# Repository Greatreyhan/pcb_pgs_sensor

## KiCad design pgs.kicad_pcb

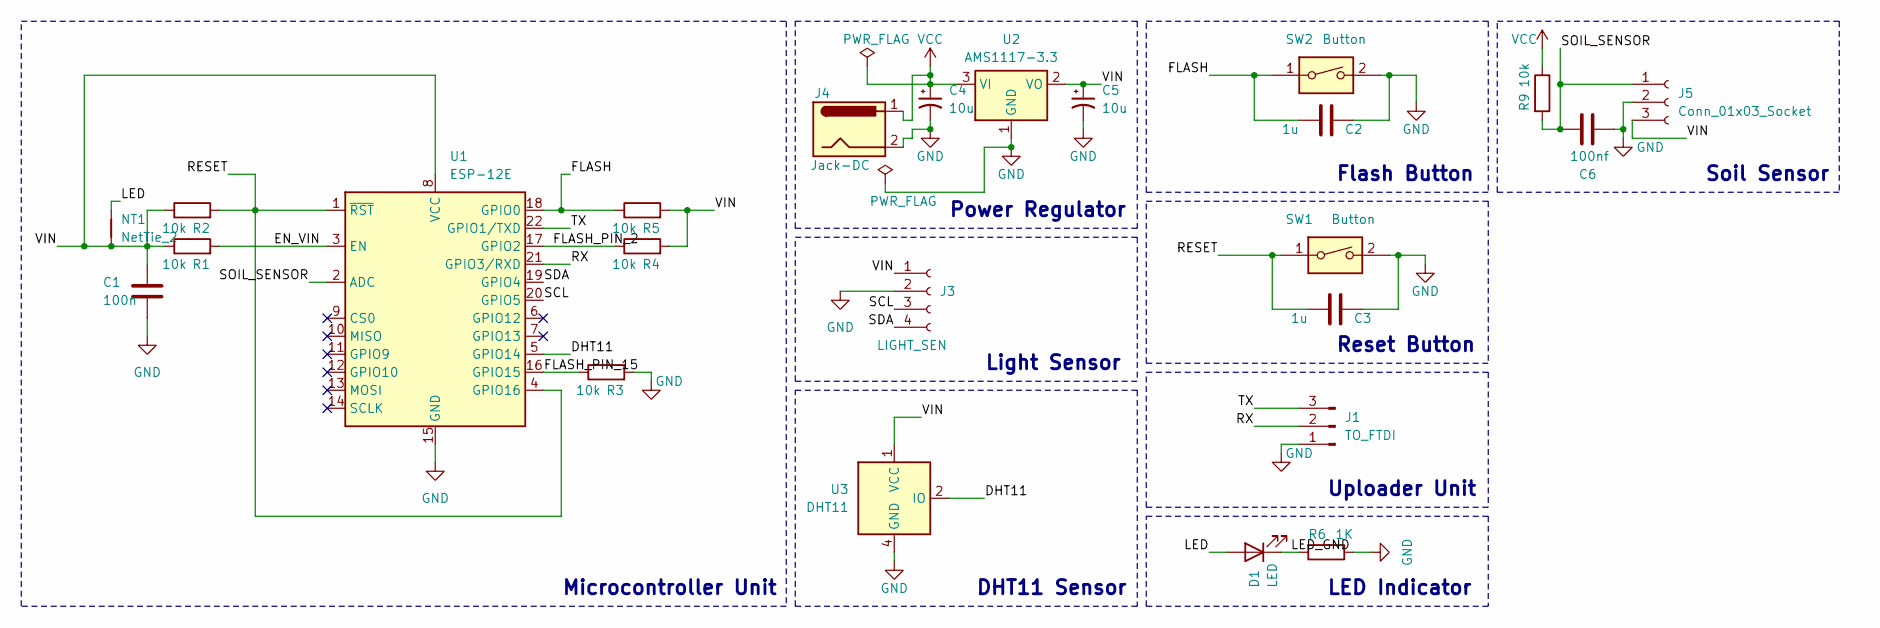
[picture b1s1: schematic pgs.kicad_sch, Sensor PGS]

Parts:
C1: 100n; C_1206_3216Metric_Pad1.33x1.80mm_HandSolder
C2, C3: 1u; C_1206_3216Metric_Pad1.33x1.80mm_HandSolder
C4, C5: 10u; CP_Elec_4x5.3
C6: 100nf; C_1206_3216Metric_Pad1.33x1.80mm_HandSolder
D1: LED; LED_1206_3216Metric_Pad1.42x1.75mm_HandSolder
J1: TO_FTDI; PinSocket_1x03_P2.54mm_Vertical
J3: LIGHT_SEN; PinHeader_1x04_P2.54mm_Vertical
J4: Jack-DC; BarrelJack_SwitchcraftConxall_RAPC10U_Horizontal
J5: Conn_01x03_Socket; PinSocket_1x03_P2.54mm_Vertical
NT1: NetTie_2; NetTie-2_THT_Pad0.3mm
R1, R2, R3, R4, R5, R9: 10k; R_1206_3216Metric_Pad1.30x1.75mm_HandSolder
R6: 1K; R_1206_3216Metric_Pad1.30x1.75mm_HandSolder
SW1, SW2: Button; SW_Push_1P1T_NO_CK_KSC6xxJ
U1: ESP-12E
U2: AMS1117-3.3; SOT-223-3_TabPin2
U3: DHT11; Aosong_DHT11_5.5x12.0_P2.54mm

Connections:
/DHT11: U1.5 (GPIO14), U3.2 (IO)
/EN_VIN: R1.2, U1.3 (EN)
/FLASH: C2.2, R5.1, SW2.1, U1.18 (GPIO0)
/FLASH_PIN_2: R4.1, U1.17 (GPIO2)
/FLASH_PIN_15: R3.1, U1.16 (GPIO15)
/LED: D1.2 (A), NT1.2
/LED_GND: D1.1 (K), R6.2
/RESET: C3.2, R2.2, SW1.1, U1.1 (~RST), U1.4 (GPIO16)
/RX: J1.2, U1.21 (GPIO3/RXD)
/SCL: J3.3, U1.20 (GPIO5)
/SDA: J3.4, U1.19 (GPIO4)
/SOIL_SENSOR: C6.2, J5.1, R9.2, U1.2 (ADC)
/TX: J1.3, U1.22 (GPIO1/TXD)
/VIN: C1.1, C5.1, J3.1, J5.3, NT1.1, R1.1, R2.1, R4.2, R5.2, U1.8 (VCC), U2.2 (VO), U3.1 (VCC)
GND: C1.2, C2.1, C3.1, C4.2, C5.2, C6.1, J1.1, J3.2, J4.2, J5.2, R3.2, R6.1, SW1.2, SW2.2, U1.15 (GND), U2.1 (GND), U3.4 (GND)
VCC: C4.1, J4.1, R9.1, U2.3 (VI)

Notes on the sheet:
LED Indicator
Uploader Unit
Flash Button
Soil Sensor
Microcontroller Unit
Light Sensor
Reset Button
DHT11 Sensor
Power Regulator

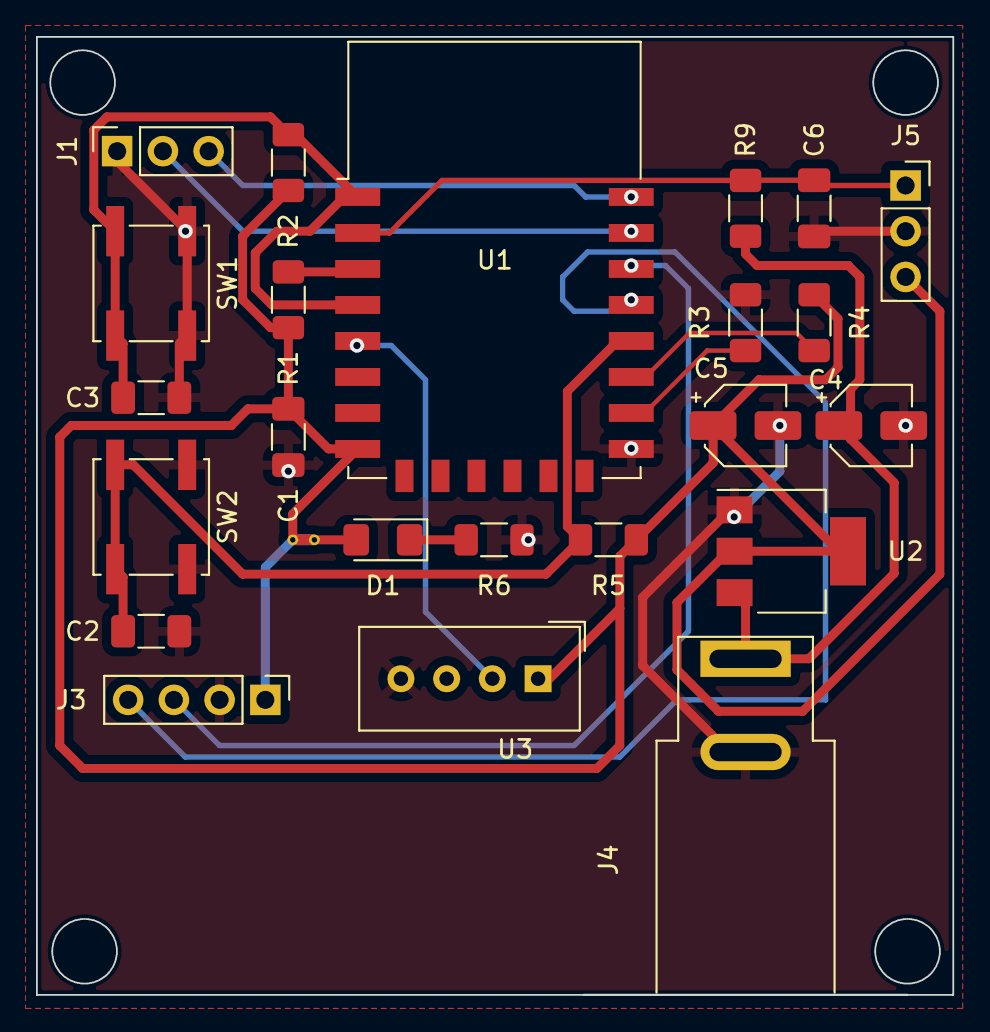
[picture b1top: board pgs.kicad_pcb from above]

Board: 2 copper layers, 50.9 x 53.2 mm, 24 parts (0 on the bottom side), 16 nets.

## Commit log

2023-08-14 problem hollow
